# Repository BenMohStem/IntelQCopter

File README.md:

# IntelQCopter · Pico architecture

C11 flight-control project for an F450/Q450 quadcopter. **Main:** RP2350 aircraft + RP2040 handheld.
[ESP32-S3/Xbox alternative](https://github.com/BenMohStem/IntelQCopter/tree/esp32-xbox).

**Prototype:** physical arming and ESC outputs remain disabled. The project has build,
CPU/emulator and simulation evidence; physical sensors, radio and flight are unvalidated.

## Start here

```powershell
.\qcopter.ps1 help
.\qcopter.ps1 build-flight
.\qcopter.ps1 build-handler
.\qcopter.ps1 build-sitl
.\qcopter.ps1 calibration-gui
.\qcopter.ps1 view-model
.\qcopter.ps1 garden -RunPrefix my-next-test
```

`garden` launches the existing native Gazebo/ROS workflow. It creates a new named run;
choose a unique prefix. Machine dependencies are documented in [Windows setup](docs/windows-jazzy-setup.md).
See [architecture and migration map](docs/architecture.md) before using an older command.

## Project map

| Area | Location |
|---|---|
| RP2350 / RP2040 C runtimes | [firmware/](firmware/README.md) |
| ROS2 C++ packages and perception | companion/ |
| Gazebo, host SITL, RP2350 emulator and plant parameters | sim/ |
| PCB draft, wiring and ESP32-S3 bench calibration | hardware/ |
| Guides and mathematical source | [docs/](docs/README.md) |
| Measurement procedures and blank worksheets | [measurements/](measurements/README.md) |
| Original logs, recordings and failed trials | artifacts/ |
| Retired Isaac and one-off setup/report scripts | [archive/](archive/README.md) |
| Local build workspace (reports, dependencies and mixed outputs) | [Inventory and cleanup boundaries](docs/build-directory-inventory-2026-11-05.md) (`build/` is ignored) |
| Download/snapshot caches / machine settings | .cache/ / .local/ (ignored) |

Tools are grouped into build, simulation, model, docs, reports, ROS2, setup and validation.
`project.json` is the command/domain catalog; `qcopter.ps1` dispatches those commands.
Open `IntelQCopter.code-workspace` for both local architecture worktrees.

## Flight design and hardware

Roll and pitch angle cascades, yaw rate control, centered-stick vertical-speed commands
with height hold; six controller objects. RT provides boost allowance. The attitude
loop target is 500 Hz; physical timing has not been measured. Battery policy: warn at
35% estimated SOC, latch disarm at 20%, with no automatic battery landing.

F450/Q450, 1400 KV motors (exact model unknown), 9047 props, four 40 A ESCs,
3S 4200 mAh / 120C LiPo. The battery's roughly 150 g is an estimate. Complete mass,
inertia, thrust/current curves and sensor noise still need measurement.
MPU6050, BMP280 and HMC5883L are planned over I²C; LoRa is the primary handheld link,
with up to two optional CC1101 channels. The user reports a TOFSense-F2 Mini
mounted centrally underneath the F450, pointing body −Z; its COM offset is still
preliminary and must be physically measured. See
[LiDAR geometry and altitude-fusion requirements](docs/lidar-geometry-and-altitude-fusion-2026-11-06.md).

## Documentation and original evidence

- [Formatted model/integration guide](docs/current-model-and-fc-integration.html)
- [Detailed mathematical paper](docs/reports/IntelQcopter-model-guide.pdf)
- [Calibration and persistent storage](docs/calibration-flash.md)
- [ESP32-S3 guided calibration GUI and QMC triage](docs/esp32-calibration-gui.md)
- [Controller input design](docs/controller-inputs.md)
- [Current missing information](docs/missing-information-and-problems.md)
- [Recorded native Gazebo video](artifacts/simulation/2026-10-20-engines/jazzy-migration-v4-gazebo.mp4)
- [Recorded graphs](artifacts/simulation/2026-10-20-engines/jazzy-migration-v4-gazebo-graphs.png)
- [Original test/emulator log index](artifacts/test-runs/README.md)

The recorded native flight used an **assumed 1.2 kg** plant and fixture-style panel
perception with simulated localization. The separate 0.740 kg component URDF is also
an assumption. Earlier PyBullet and Isaac results retain their original engine labels.
The old line-by-line walkthrough is pinned to a historical source commit.

The ESP32 branch's newer linear/discrete tutorial and QEMU results are separate from
these Pico results. Select that worktree for its active code and launch commands.

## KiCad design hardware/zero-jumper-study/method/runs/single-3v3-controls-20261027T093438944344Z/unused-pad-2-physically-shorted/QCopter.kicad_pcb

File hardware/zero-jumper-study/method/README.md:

# Can this single-sided layout satisfy the specification?

Use **necessary tests first, a complete routed witness second, and physical
measurements last**. A failed autorouter run means that run failed. It does not
prove that every placement, GPIO assignment or continuous route is impossible.

## Requirements that this gate checks

| Requirement | CAD acceptance |
|---|---|
| Required parts | Exactly U1 ESP32, U2 MPU, U3 BMP, U4 compass, J1 lidar and J2–J5 ESC headers |
| Manufactured interface | 79 unique through holes, correct module pin ordering/pitch, round solder lands at least 2 mm, annulus at least 0.45 mm |
| Home fabrication | B.Cu tracks/pours only; tracks at least 1.2 mm; explicit clearance at least 0.5 mm; no vias or hidden copper graphics |
| Zero wire bridges | No extra jumper components, net ties, internal pad-jumper declarations or duplicate pin tricks |
| Ground | Every required GND endpoint belongs to one **actual carrier-copper** component |
| Power | 3.3 V sensors and I2C; 5 V FC/lidar; exactly one ESC BEC positive feeds 5 V; other BEC positives isolated |
| GPIO | Unique eligible ESP32-S3 GPIO for each signal; exclude boot, USB, flash/PSRAM and board-LED conflicts |
| Antenna | No copper intersects the nominal antenna projection; permanent F.Cu/B.Cu rule area covers the entire nominal antenna projection and blocks tracks, vias, pads and pours |
| Native tools | Zero native DRC, unconnected items and schematic parity issues; native XML agrees with PCB nets |

BMP280 SDO is deliberately selectable: `--bmp-address 0x76` requires SDO=GND
and counts 14 ground endpoints. `--bmp-address 0x77` requires SDO=3V3 and counts
13. Bosch documents both choices; the future driver must use the selected
address. SDO cannot float and CSB remains at 3.3 V for I2C. This option does not
change the current bench firmware. [Bosch BMP280 datasheet](https://www.bosch-sensortec.com/media/boschsensortec/downloads/datasheets/bst-bmp280-ds001.pdf)

The carrier numbering is checked against the genuine DevKitC-1 header map,
including the two 22-pin rows and 22.86 mm spacing. Candidate GPIO reassignment
is allowed, but changing a net name cannot turn an unsuitable GPIO into a valid
output. GPIO40/41 must not simultaneously serve external JTAG. Actual clone
variant and purchased dimensions remain unverified.
[Espressif header reference](https://docs.espressif.com/projects/esp-dev-kits/en/latest/esp32s3/esp32-s3-devkitc-1/user_guide_v1.0.html)

An explicitly selected `--single-3v3-pad 1` or `--single-3v3-pad 2` may use one
of the DevKit's duplicate 3.3 V output headers and leave the other **unconnected
on the carrier**. Both are on the same internal DevKit supply rail; using one
output is an ordinary carrier power choice, not a hidden ground bridge.
The default still requires both carrier connections. The optional mode checks
the unused pad has no touching carrier copper and checks that every sensor
VCC/CSB/selected-SDO endpoint is physically connected to the used output by
carrier copper. All ground endpoints remain mandatory bare-copper connections.
[Espressif DevKit schematic](https://dl.espressif.com/dl/schematics/SCH_ESP32-S3-DevKitC-1_V1.1_20220413.pdf)

## 1. Reject impossible pin escapes before routing

For neighbouring round pads, let pitch be `p`, diameter `d`, track width `w`
and copper clearance `c`. The available gap is

\[
g=p-d.
\]

A different-net track can pass through that gap only if

\[
w+2c\leq g.
\]

Here

\[
g=2.54-2.00=0.54\ \mathrm{mm},\qquad
w+2c=1.20+2(0.50)=2.20\ \mathrm{mm}.
\]

Therefore these header banks **cannot be crossed between adjacent pads** by a
1.2 mm different-net track. Escape through the appropriate terminal or around
the bank ends. Raising a sensor permits routing beneath its body; it does not
create additional space between the solder pads.

## 2. Test narrow channels and terminal order

If `n` distinct nets are forced through a channel of usable width `W`, then a
necessary packing condition is

\[
nw+(n-1)c+2b\leq W,
\qquad
n\leq\left\lfloor\frac{W-2b+c}{w+c}\right\rfloor,
\]

where `b` is clearance to each channel boundary. With `W=6`, `w=1.2`, `c=b=0.5`
mm, at most three such tracks fit. Four forced nets require 7.3 mm and cannot
use that fixed channel. This is a certificate **only if an alternative path
around the channel is excluded**. Moving a module or changing a GPIO can remove
the forced cut. Published routing work uses channel density as a lower bound,
not as a general feasibility certificate.
[Princeton routing research](https://www.cs.princeton.edu/research/techreps/746),
[Berkeley routing lecture](https://people.eecs.berkeley.edu/~keutzer/classes/244fa2005/lectures/4-routing.pdf)

For two two-terminal nets constrained to one simply connected region, alternating
boundary order `A1,B1,A2,B2` forces a crossing: an A1–A2 path divides the region,
and the two B terminals lie on opposite sides. This does not apply if a route
may leave the region, pass under an assumed obstacle, or use an allowed alternate
terminal. It is a local, stated-boundary test.

Do **not** collapse every multi-pin module into one graph vertex and call a
nonplanar component-net graph a proof of impossibility. Independent module pins
are not shorted together, and legal traces may pass beneath raised modules.
The actual ports, obstacles, channel boundaries and net-tree choices matter.

## 3. Reserve power and ground corridors

Choose placements and GPIOs that put sensor bus terminals in compatible orders.
Reserve escape corridors before committing long signal trees. Ground-first or
signal-first routing are heuristics; neither guarantees success. After every
complete signal-route/RF-keepout iteration, refill native zones and reconstruct
ground connectivity again. A signal path or antenna cutout can split a ground
pour even when every pad still displays the label `GND`.

The independent graph in `geometry.py` uses actual round pads, finite-width
segments and individual filled-zone contours/holes. Separate islands receive
separate vertices. It does not add edges for ESP internal wiring, net labels,
jumper pad settings, schematic components or 3D models. Native DRC/parity is
also mandatory: the independent geometry calculation is an additional check,
not a replacement for KiCad's engine.

KiCad explicitly distinguishes copper net ties from pad jumpers that assume
off-board component connections. Both are rejected for this zero-jumper carrier
test. This prevents an apparently clean ratsnest from hiding a wire or module
ground path. [KiCad 10 pad connection documentation](https://docs.kicad.org/10.0/en/pcbnew/pcbnew.html#_pad_connections_net_ties_and_jumper_pads)

## 4. Require a complete witness, not a promising partial board

Run from the Stepwise checkout, with KiCad's bundled Python:

```powershell
& "$env:LOCALAPPDATA\Programs\KiCad\10.0\bin\python.exe" `
  tools\pcb_zero_jumper\method\validate_zero.py `
  hardware\zero-jumper-study\layout-a\YOUR-CANDIDATE `
  --report-dir hardware\zero-jumper-study\method\runs\candidate-a
```

For the deliberately high BMP SDO option, add `--bmp-address 0x77`.
If the approved duplicate power-output option is used, also add
`--single-3v3-pad 1` (or `2`, matching the candidate's used output).
The report directory retains the exact native DRC JSON, XML netlist, original
native tool output, board SHA256 and every independent check. Exit code zero
means scoped CAD acceptance only. `--skip-native` is useful during construction
but intentionally **cannot** return final acceptance.

An exact SMT/ILP/exhaustive router could prove `UNSAT` for a fully specified
finite grid, placements, net-tree choices and rules. That proof excludes only
that formal model. It does not exclude continuous routes, other grid spacing,
other legal GPIOs or other placements unless those were represented. A timeout
or bounded heuristic search gives no impossibility proof.

## Recorded controls and limits

- [14 analytic controls](analytic-controls.json) pass: disjoint same-labelled
  copper stays disconnected, a real track joins pads, polygon holes remain
  holes, and channel/order lower bounds reject the intended impossible cases.
- [Current jumper board negative control](runs/current-jumper-negative-control/report.json)
  is correctly **rejected** as zero-jumper even though its native DRC/parity
  pass. It has real wire components, additional holes and physically separated
  carrier ground groups. Its assembled three-wire acceptance remains a separate
  claim; this test does not invalidate that documented assembly.

No new zero-jumper candidate has been accepted by this method yet. Layout A/B
remain separate search tasks until complete native results are supplied.

Nominal antenna projection is not a certified 15 mm air/copper clearance. The
preferred module placement puts the antenna beyond the carrier edge; verify
housing, installed modules and cables, then measure actual RF range. Copper
clearance alone cannot predict antenna performance.
[Espressif antenna guidance](https://docs.espressif.com/projects/esp-hardware-design-guidelines/en/latest/esp32s3/pcb-layout-design.html)

Even final CAD acceptance does not establish actual clone pinout/dimensions,
print scale, etching, drilling, solder continuity, current capacity, supply noise,
I2C rise times/pullups, lidar logic levels, ESC PWM thresholds or flight safety.
Measure these on the real assembly before enabling motor outputs. Motor arming
remains disabled; this study performs no flashing or actuator operations.

## Additional 3.3 V and antenna-rule controls

The optional single-output policy has [seven native-board pin/short controls](runs/single-3v3-controls/controls.json)
and [three synthetic copper-power controls](runs/single-3v3-power-controls/controls.json).
These checks include both selected-pin choices, the default two-pin policy, a
wrong selection, an unused pad touched by carrier copper, and an isolated sensor
VCC. All pass. The test boards are intentionally incomplete, native DRC is skipped
for these focused checks, and none is approved for manufacturing.

The antenna gate subtracts the actual qualifying KiCad rule polygons from the
nominal antenna projection. Merely having a rule area elsewhere cannot pass it.
The [RF rule-coverage controls](runs/rf-rule-coverage-controls.json) exercise
complete, partial, unrelated, union-of-two, and hole-in-keepout cases. RF range,
the real module antenna shape, nearby housing and the recommended physical
clearance around the antenna remain separate measurements.

The strengthened validator was also run on the [current RF-clearance carrier](runs/current-rf-jumper-negative-final/report.json).
Native DRC, unconnected items and schematic parity are all zero, and its antenna
rule covers the nominal projection; it is correctly rejected by the separate
zero-wire criterion because it physically uses ground jumpers. This confirms
that an electrically valid assembled three-wire board is not mistaken for a
bare-copper zero-jumper design.

Each inline sensor header is checked for a straight, ordered, uniformly spaced
row, not merely for distances from pin 1. [Header controls](runs/inline-header-controls.json)
include rotated valid rows and curved or misordered invalid rows. Actual module
outline, pin labels and physical orientation still require checking the purchased
boards; this geometric check cannot certify a clone's body dimensions.

Re-run the focused controls from the Stepwise checkout with the KiCad Python
interpreter. They save new timestamped evidence and never overwrite earlier runs:

```powershell
$kicadPython = "$env:LOCALAPPDATA\Programs\KiCad\10.0\bin\python.exe"
& $kicadPython tools\pcb_zero_jumper\method\test_single_3v3.py
& $kicadPython tools\pcb_zero_jumper\method\test_single_3v3_power.py
& $kicadPython tools\pcb_zero_jumper\method\test_rf_coverage.py
& $kicadPython tools\pcb_zero_jumper\method\test_inline_header.py
```

The generated test boards are **synthetic, incomplete fixtures**. They are not
finished PCB candidates, and no native DRC acceptance is claimed for them.

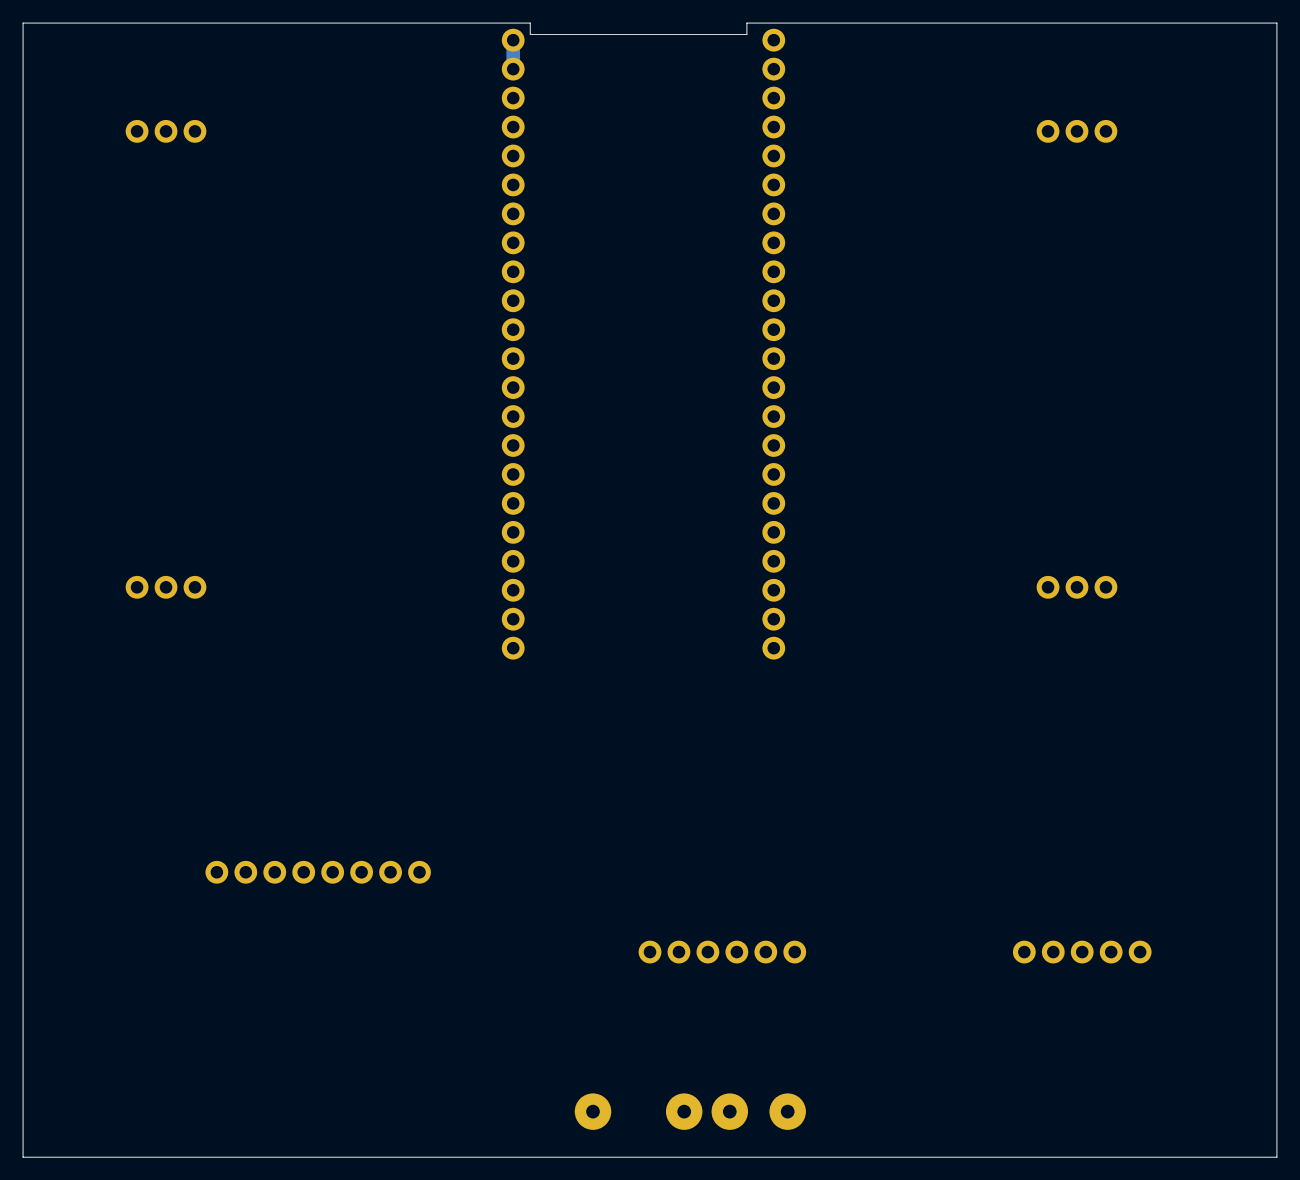
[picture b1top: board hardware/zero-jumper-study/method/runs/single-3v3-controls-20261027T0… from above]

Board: 2 copper layers, 110.0 x 99.5 mm, 9 parts (0 on the bottom side), 15 nets.

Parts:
J1: LIDAR_SOLDER_WIRES; Lidar_Free_Solder_Lands
J2, J3, J4, J5: ESC_Servo_1x03
U1: ESP32_S3_DevKitC_1_44pin
U2: MPU6050_GY521_1x08
U3: BMP280_GY_1x06
U4: Magnetometer_GY271_1x05

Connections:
3V3: U1.1, U2.1, U3.1, U3.5, U3.6, U4.1
ESC1_SIGNAL: J5.3, U1.4
ESC2_SIGNAL: J2.3, U1.40
ESC3_SIGNAL: J4.3, U1.11
ESC4_SIGNAL: J3.3, U1.27
FC_5V: J1.1, J4.2, U1.21
FC_TX_TO_LIDAR: J1.4, U1.9
GND: J1.2, J2.1, J3.1, J4.1, J5.1, U1.22, U1.23, U1.24, U1.44, U2.2, U2.7, U3.2, U4.2
LIDAR_TO_FC_RX: J1.3, U1.8
MAG_DRDY: U1.38, U4.5
MPU_INT: U1.20, U2.8
MPU_SCL: U1.18, U2.3
MPU_SDA: U1.19, U2.4
SLOW_SCL: U1.37, U3.3, U4.3
SLOW_SDA: U1.36, U3.4, U4.4

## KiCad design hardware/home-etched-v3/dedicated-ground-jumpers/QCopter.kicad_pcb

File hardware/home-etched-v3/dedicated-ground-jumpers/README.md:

# Current PCB: antenna clearance and three GND wires

Open [QCopter.kicad_pro](QCopter.kicad_pro) / [PCB](QCopter.kicad_pcb), then
press **Alt+3**. The marked antenna-side edge now has an **11 mm copper-free
strip** across the carrier. The central antenna projection is also protected.
The rule area forbids copper fill, tracks, vias and pads on both copper layers.
The FR4 board remains; this is copper removal, not a board cutout.

[Current three-copy 1:1 mask](output/etch-mask-3-copies-A4-1to1.pdf) ·
[Labelled assembly guide](output/assembly-guide.html) ·
[3D preview](output/3d-bottom.png) ·
[Portable KiCad ZIP](output/IntelQCopter-dedicated-ground-jumpers-KiCad.zip)

## Fit the three ground wires

Clearing the top copper removed a former ground bridge. **G2 now has THREE
dedicated holes**, so every ground still becomes common using three wires.
It is one continuous insulated wire; strip its middle solder point as marked.
Use fine wire that fits the 1.2 mm holes (for example AWG24), verifying its
actual diameter before soldering. No wire shares a module/ESC header hole.

| Wire | Dedicated holes, in physical wire order |
|---|---|
| G1 | G1.1 (112,79) -> G1.2 (118.5,60.5) mm |
| G2 | G2.3 (124,60.5) -> G2.1 (103,108.6), middle tap -> G2.2 (103,117.4) mm |
| G3 | G3.1 (55,108) -> G3.2 (55,117.4) mm |

G2 joins the RF-side ground, right ESC return and common ground. G1's sensor
ground reaches common ground through G2. All three wires and all seven solder
points are mandatory. G1/G2 pass below raised sensor modules: fit wires first,
keep them below the assumed 9 mm module height and verify actual clearance.

## Evidence and limits

[Native DRC/parity](validation/rf-clearance/drc.json): **0 violations,
0 unconnected items, 0 schematic mismatches**. The independent
[native pad/wire graph](verification.json) verifies all fourteen logical GND
endpoints common after fitting the wires. Carrier ground paths do not depend
on undocumented connections inside the ESP module. Rejected placement/return
trials are retained under validation. No errors were waived for this change.

There are **86 drilled holes**: 79 original module/header holes and 7 dedicated
jumper holes. Lands are 3.2 mm with 1.2 mm drill for wires. B.Cu is the only
routed layer, tracks >=1.2 mm, clearance >=0.5 mm. GPIO/I2C/UART/PWM assignments
remain those in the [pin audit](pin-audit.md); physical ground aliases changed.
No firmware, flashing, sensor calibration or motor arming changes.

Print the NEW mask at Actual size / 100%, no Fit or extra mirror. Three
92 x 82 mm vector copies on A4, black retained copper, white drills, no text.
Older masks do not include this clearance or the new G2.3 hole.

This is the requested practical carrier clearance, **not proof of full 15 mm
RF clearance or better measured range**. Espressif recommends placing the
antenna outside the baseboard or providing sufficient clearance and testing
the finished assembly: [official guidance](https://docs.espressif.com/projects/esp-hardware-design-guidelines/en/latest/esp32s3/pcb-layout-design.html).
Clone fit, housing, nearby wires, etching, printer scale and actual RF remain
unverified. With power disconnected, check every ground against lidar GND and
check 5 V / 3.3 V for shorts before power.

Only the selected J4/ESC3 regulated 5 V BEC feeds the carrier. Keep other BEC
positives isolated; disconnect it before USB power. High motor/battery current
stays on a separate PDB. Physical motor arming remains disabled.

Prior three-pair revision is preserved in Git commit ad9e6b3. Fresh zero-jumper
layout candidates are separate studies until all acceptance checks pass.

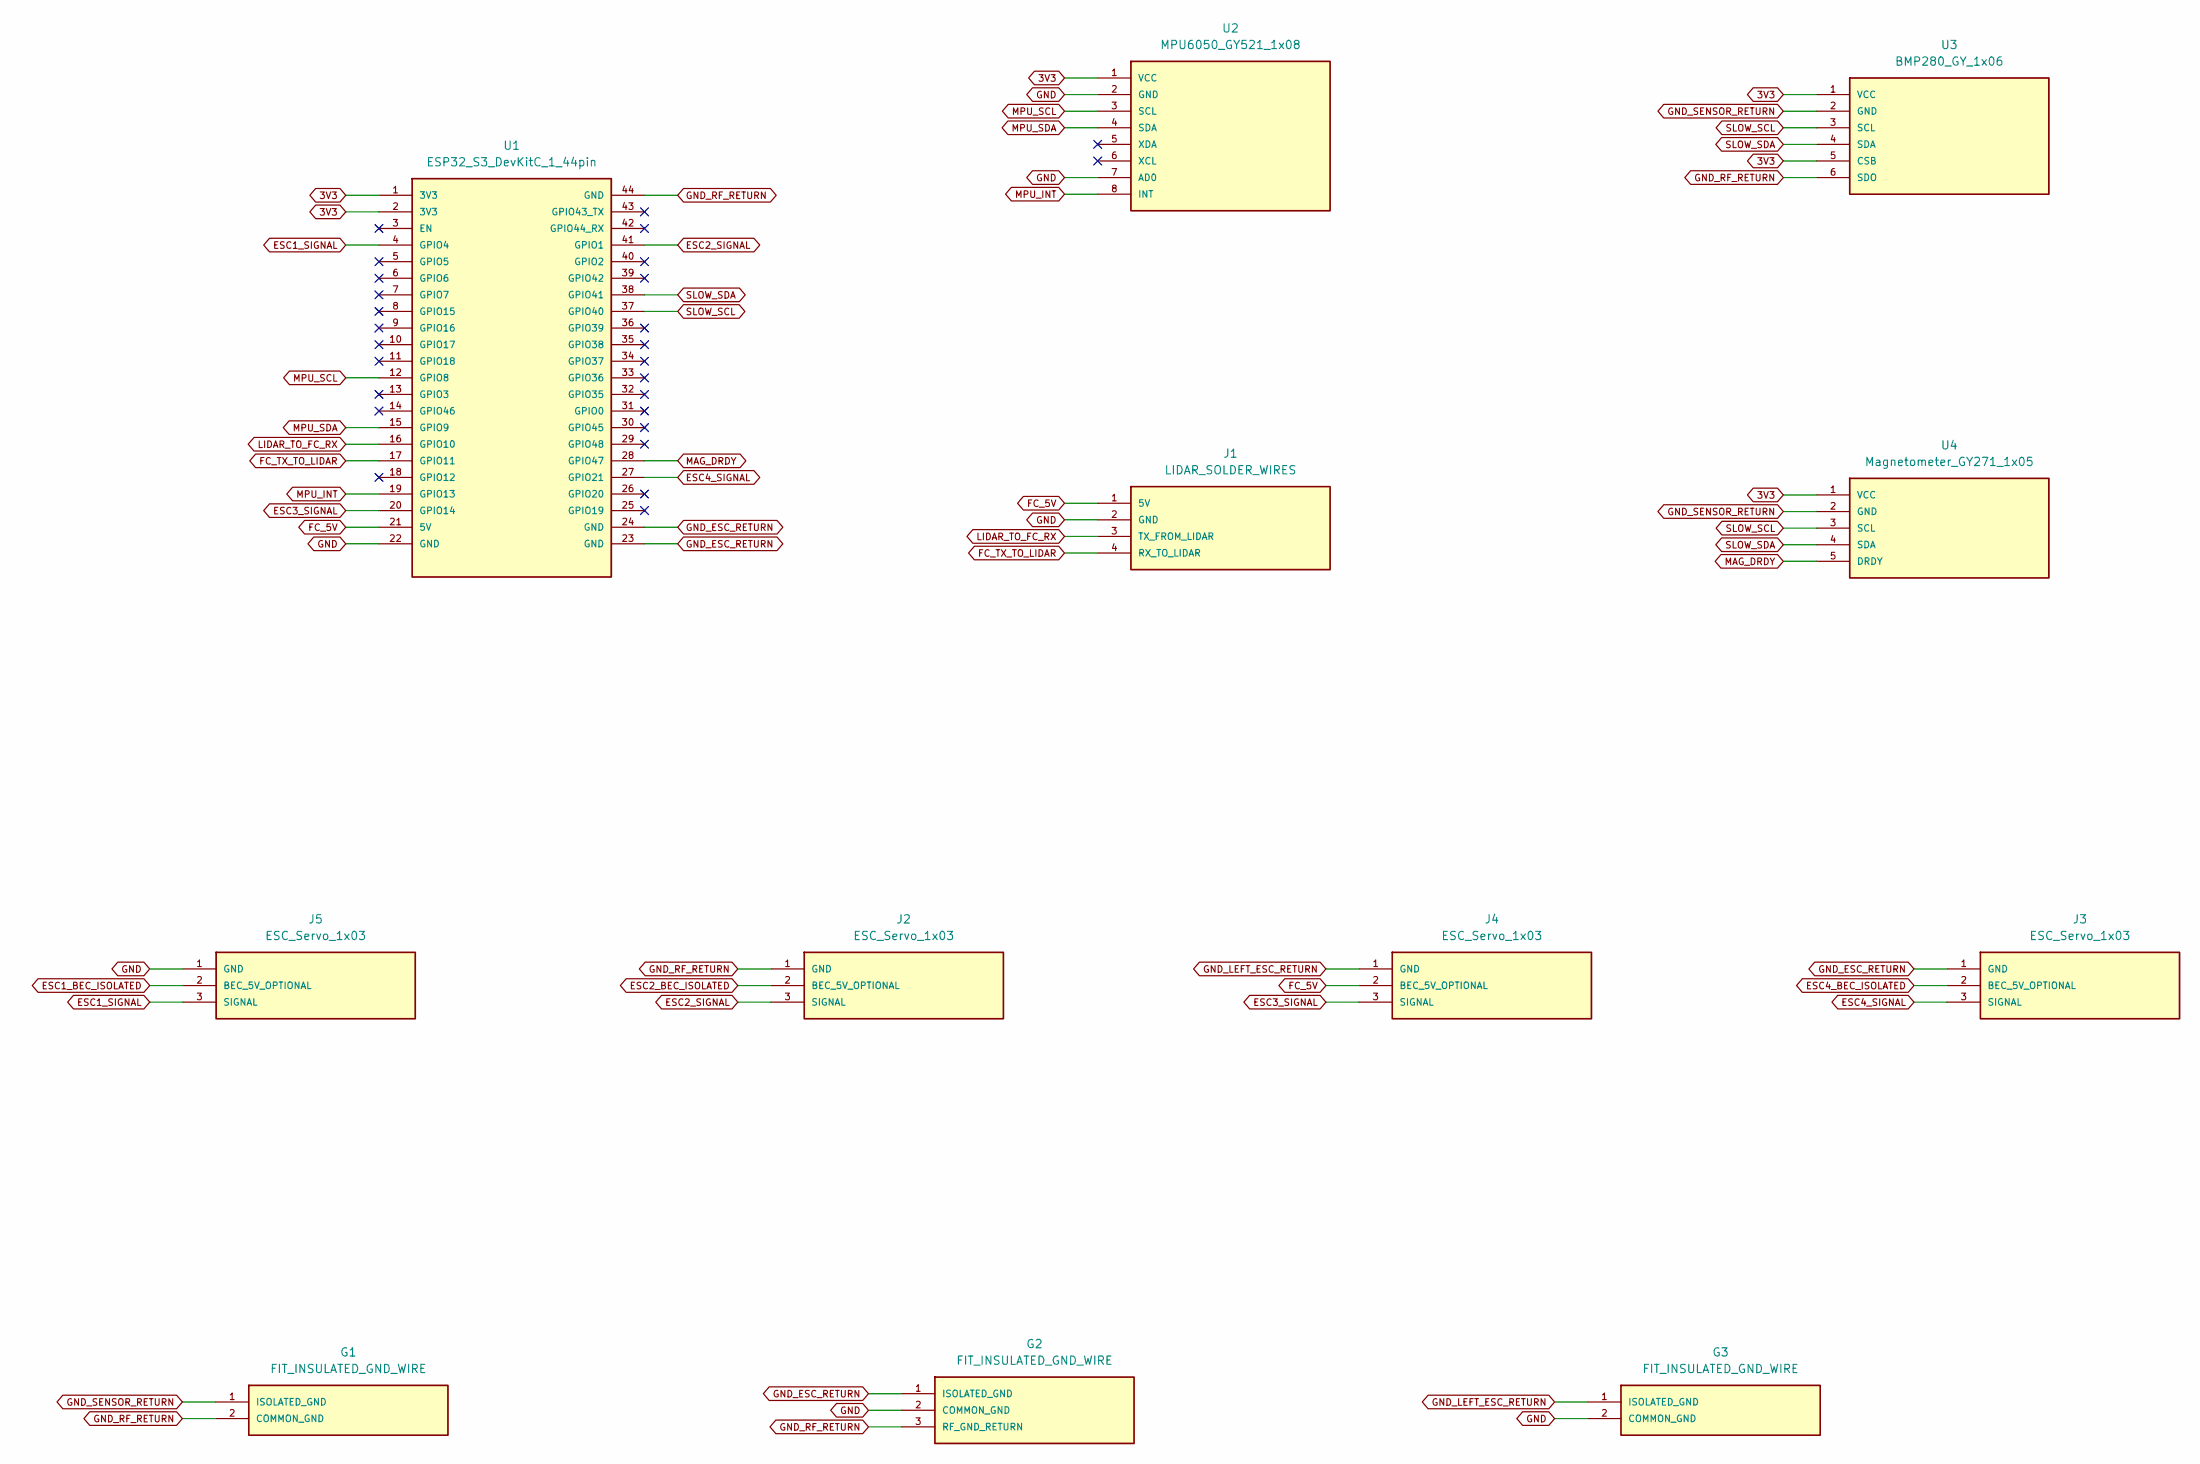
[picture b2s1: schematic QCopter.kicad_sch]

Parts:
G1: FIT_INSULATED_GND_WIRE; Ground_Jumper_G1
G2: FIT_INSULATED_GND_WIRE; Ground_Jumper_G2
G3: FIT_INSULATED_GND_WIRE; Ground_Jumper_G3
J1: LIDAR_SOLDER_WIRES; Lidar_Free_Solder_Lands
J2, J3, J4, J5: ESC_Servo_1x03
U1: ESP32_S3_DevKitC_1_44pin
U2: MPU6050_GY521_1x08
U3: BMP280_GY_1x06
U4: Magnetometer_GY271_1x05

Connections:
3V3: U1.1 (3V3), U1.2 (3V3), U2.1 (VCC), U3.1 (VCC), U3.5 (CSB), U4.1 (VCC)
ESC1_BEC_ISOLATED: J5.2 (BEC_5V_OPTIONAL)
ESC1_SIGNAL: J5.3 (SIGNAL), U1.4 (GPIO4)
ESC2_BEC_ISOLATED: J2.2 (BEC_5V_OPTIONAL)
ESC2_SIGNAL: J2.3 (SIGNAL), U1.41 (GPIO1)
ESC3_SIGNAL: J4.3 (SIGNAL), U1.20 (GPIO14)
ESC4_BEC_ISOLATED: J3.2 (BEC_5V_OPTIONAL)
ESC4_SIGNAL: J3.3 (SIGNAL), U1.27 (GPIO21)
FC_5V: J1.1 (5V), J4.2 (BEC_5V_OPTIONAL), U1.21 (5V)
FC_TX_TO_LIDAR: J1.4 (RX_TO_LIDAR), U1.17 (GPIO11)
GND: G2.2 (COMMON_GND), G3.2 (COMMON_GND), J1.2 (GND), J5.1 (GND), U1.22 (GND), U2.2 (GND), U2.7 (AD0)
GND_ESC_RETURN: G2.1 (ISOLATED_GND), J3.1 (GND), U1.23 (GND), U1.24 (GND)
GND_LEFT_ESC_RETURN: G3.1 (ISOLATED_GND), J4.1 (GND)
GND_RF_RETURN: G1.2 (COMMON_GND), G2.3 (RF_GND_RETURN), J2.1 (GND), U1.44 (GND), U3.6 (SDO)
GND_SENSOR_RETURN: G1.1 (ISOLATED_GND), U3.2 (GND), U4.2 (GND)
LIDAR_TO_FC_RX: J1.3 (TX_FROM_LIDAR), U1.16 (GPIO10)
MAG_DRDY: U1.28 (GPIO47), U4.5 (DRDY)
MPU_INT: U1.19 (GPIO13), U2.8 (INT)
MPU_SCL: U1.12 (GPIO8), U2.3 (SCL)
MPU_SDA: U1.15 (GPIO9), U2.4 (SDA)
SLOW_SCL: U1.37 (GPIO40), U3.3 (SCL), U4.3 (SCL)
SLOW_SDA: U1.38 (GPIO41), U3.4 (SDA), U4.4 (SDA)

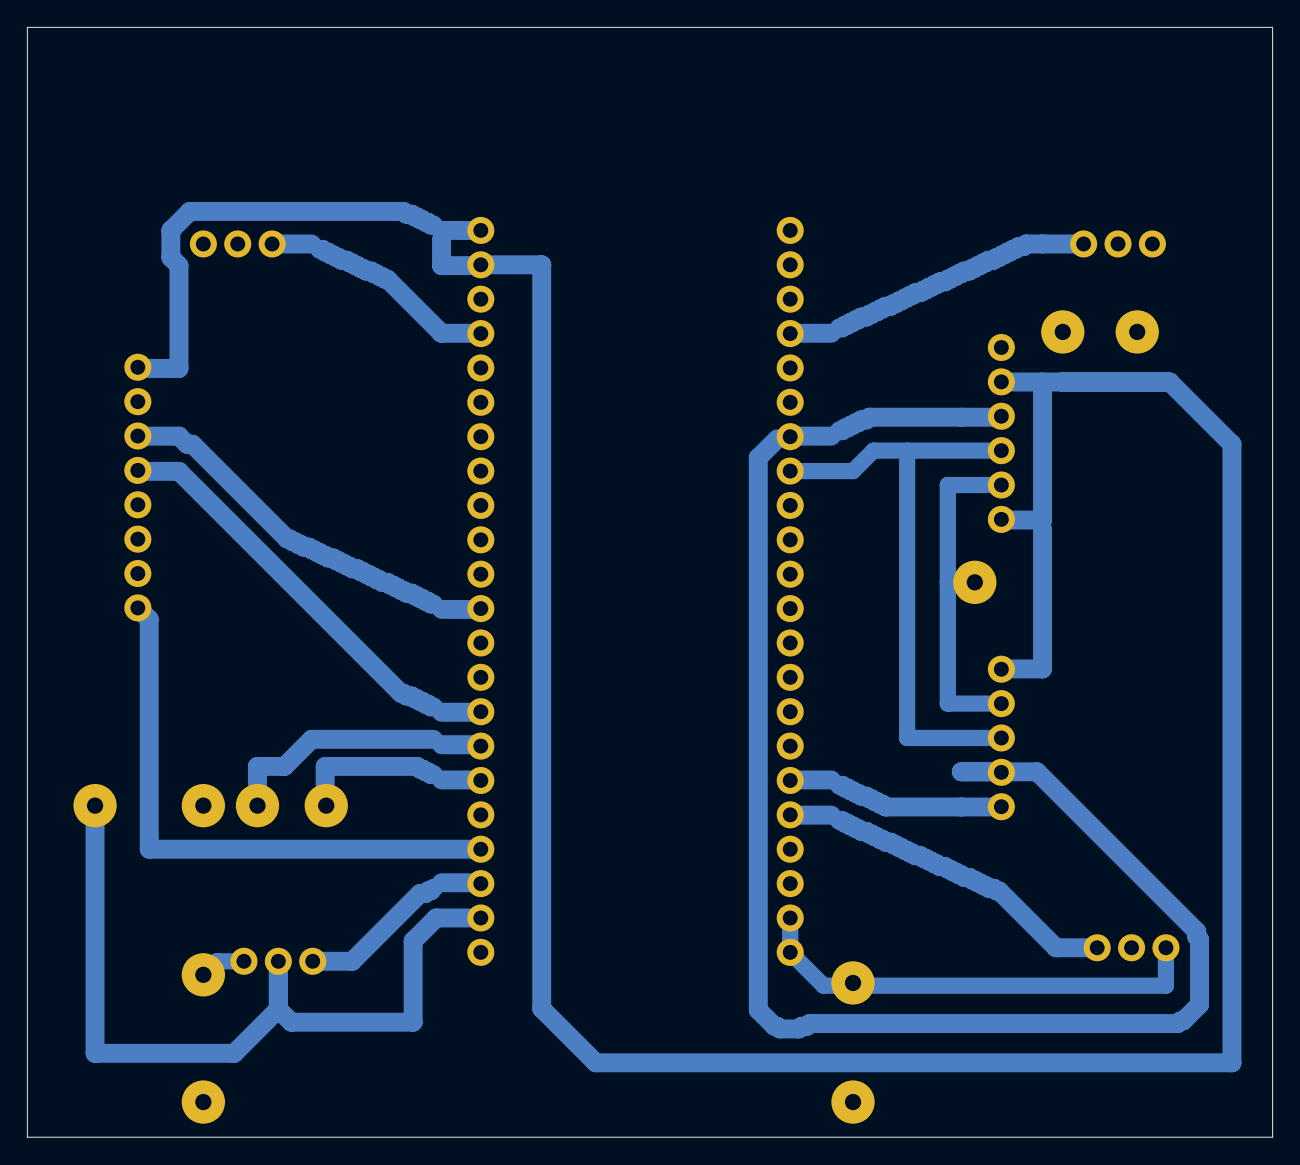
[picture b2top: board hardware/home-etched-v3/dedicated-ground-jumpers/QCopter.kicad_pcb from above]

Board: 2 copper layers, 92.0 x 82.0 mm, 12 parts (0 on the bottom side), 19 nets.
